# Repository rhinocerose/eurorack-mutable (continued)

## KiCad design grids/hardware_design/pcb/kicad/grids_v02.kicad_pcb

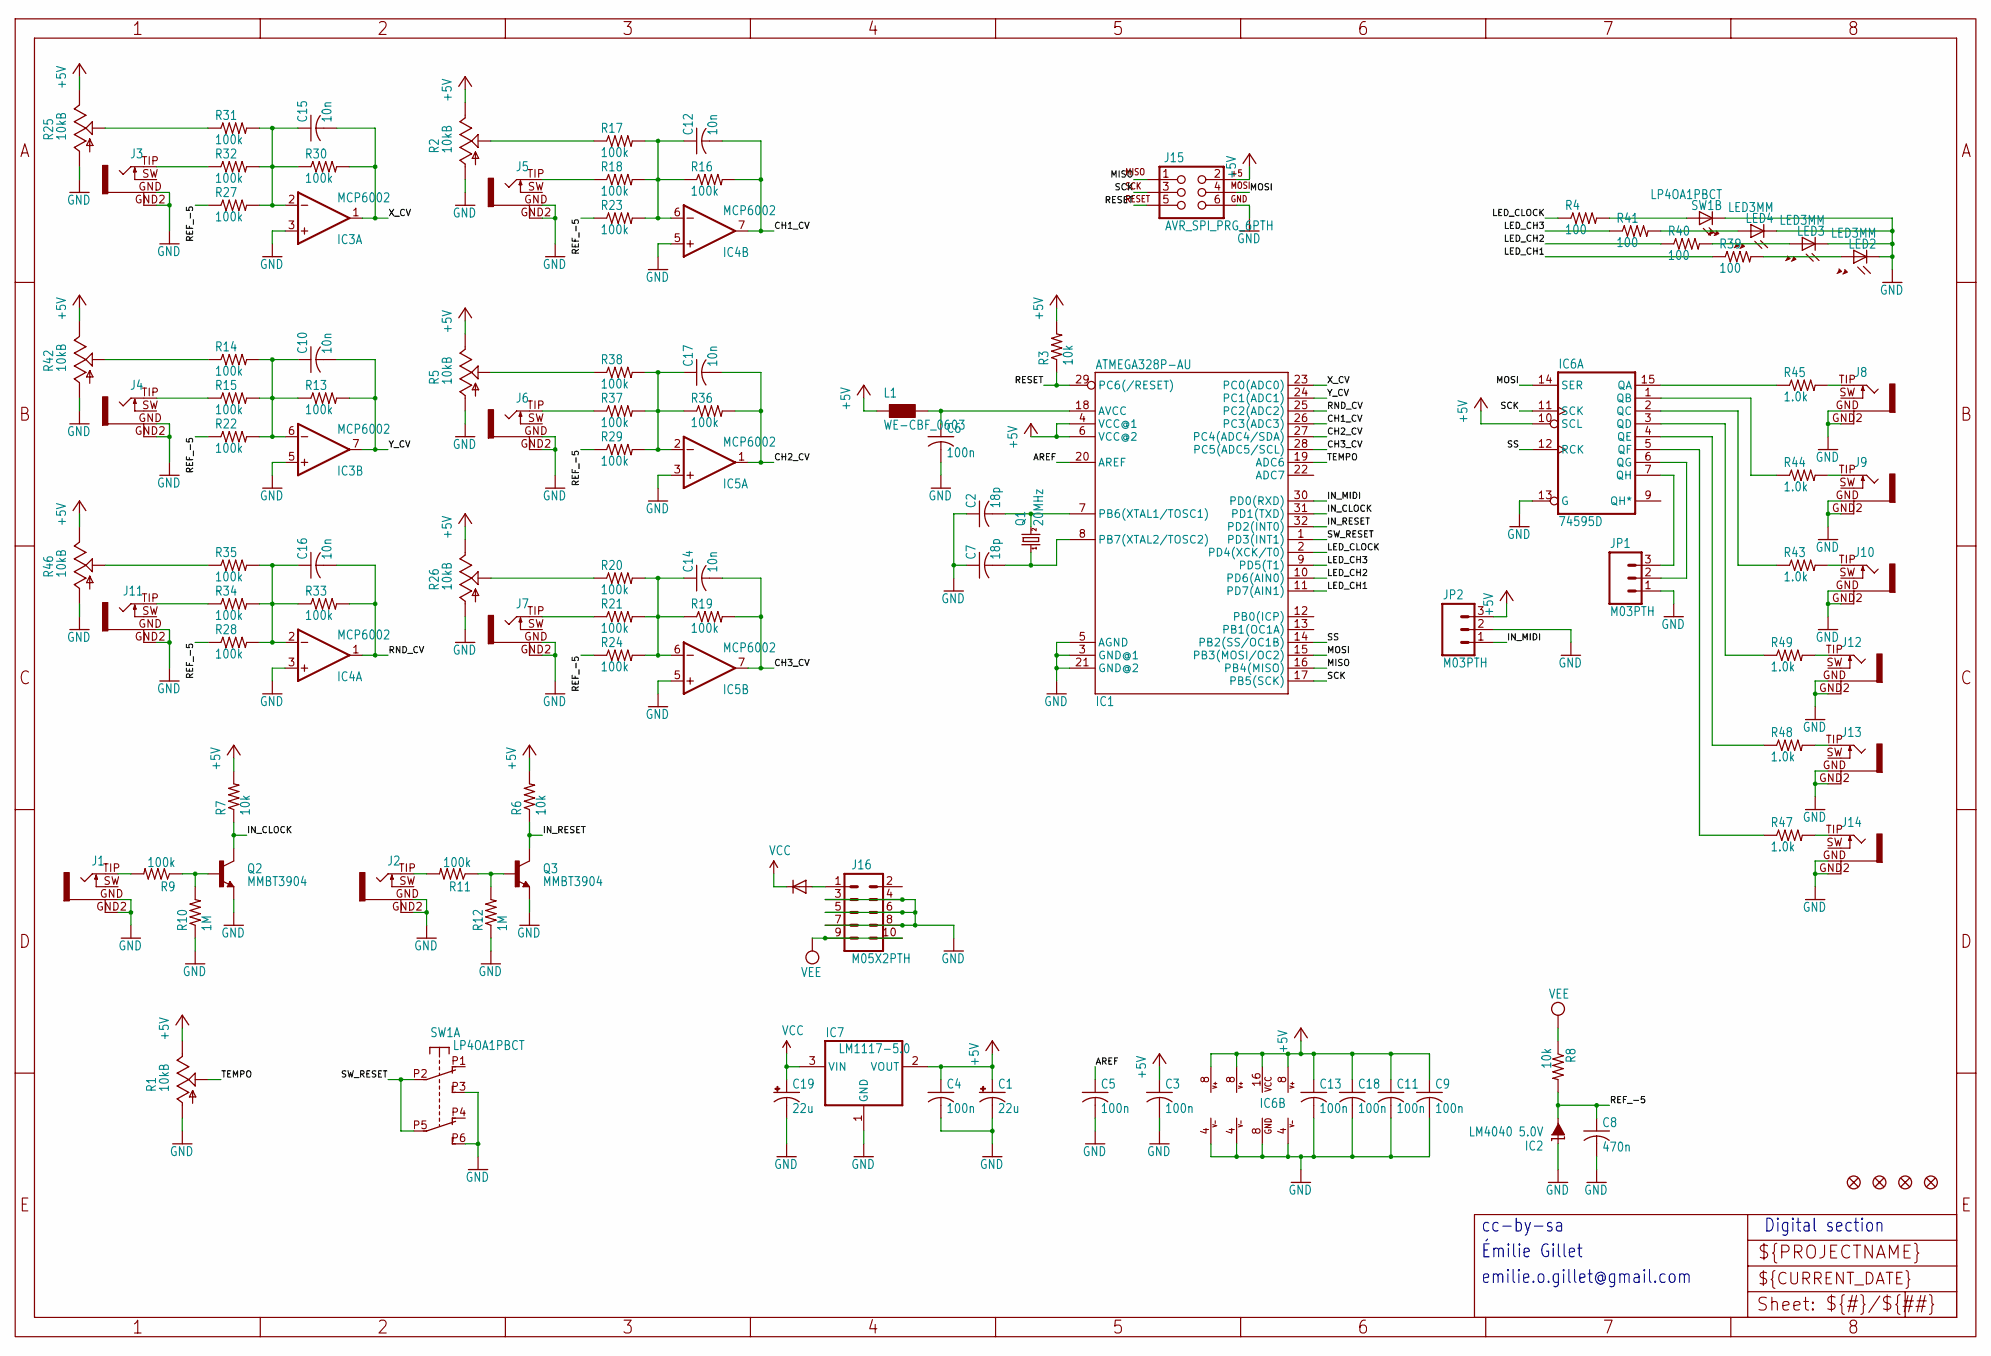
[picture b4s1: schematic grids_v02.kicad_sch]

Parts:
C1, C19: 22u; PANASONIC_C
C2, C7: 18p; C0603
C3, C4, C5, C6, C9, C11, C13, C18: 100n; C0603
C8: 470n; C0603
C10, C12, C14, C15, C16, C17: 10n; C0603
D1: 1N5819HW; SOD123
F1, F2, F3, F4: FIDUCIAL1X2; FIDUCIAL-1X2
IC1: ATMEGA328P-AU; TQFP32-08
IC2: LM4040 5.0V; DBZ_R-PDSO-G3
IC3, IC4, IC5: MCP6002; SO08
IC6: 74595D; SO16
IC7: LM1117-5.0; SOT223
J1, J2, J3, J4, J5, J6, J7, J8, J9, J10, J11, J12, J13, J14: PJ301WQP; WQP_PJ_301BM
J15: AVR_SPI_PRG_6PTH; 2X3
J16: M05X2PTH; AVR_ICSP
JP1, JP2: M03PTH; 1X03
L1: WE-CBF_0603; 0603
LED2, LED3, LED4: LED3MM
Q1: 20MHz; HC49UP
Q2, Q3: MMBT3904; SOT23-BEC
R1, R2, R5, R25, R26, R46: 10kB; ALPS_POT_VERTICAL_PS
R3, R6, R7, R8: 10k; R0603
R4, R39, R40, R41: 100; R0603
R9, R11, R13, R14, R15, R16, R17, R18, R19, R20, R21, R22, R23, R24, R27, R28, R29, R30, R31, R32, R33, R34, R35, R36, R37, R38: 100k; R0603
R10, R12: 1M; R0603
R42: 10kB; ALPS_POT_VERTICAL_PS4
R43, R44, R45, R47, R48, R49: 1.0k; R0603
SW1: LP4OA1PBCT

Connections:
+5V: C1.+, C3.1, C4.1, C9.1, C11.1, C13.1, C18.1, IC1.4 (VCC@1), IC1.6 (VCC@2), IC3.8 (V+), IC4.8 (V+), IC5.8 (V+), IC6.10 (SCL), IC6.16 (VCC), IC7.2 (VOUT), J15.2, JP2.3, L1.1, R1.P$1 (E), R2.P$1 (E), R3.2, R5.P$1 (E), R6.2, R7.2, R25.P$1 (E), R26.P$1 (E), R42.P$1 (E), R46.P$1 (E)
AREF: C5.1, IC1.20 (AREF)
CH1_CV: C12.2, IC1.26 (PC3(ADC3)), IC4.7 (OUT), R16.2
CH2_CV: C17.2, IC1.27 (PC4(ADC4/SDA)), IC5.1 (OUT), R36.2
CH3_CV: C14.2, IC1.28 (PC5(ADC5/SCL)), IC5.7 (OUT), R19.2
CLOCK_OUT: IC6.6 (QG), JP1.2
GATE1_IN: J1.TIP (2), R9.2
GATE1_LED: R4.2, SW1.L1
GATE2_IN: J2.TIP (2), R11.2
GATE2_LED: LED4.A, R41.2
GATE3_LED: LED3.A, R40.2
GATE4_LED: LED2.A, R39.2
GND: C1.-, C2.1, C3.2, C4.2, C5.2, C6.2, C7.1, C8.2, C9.2, C11.2, C13.2, C18.2, C19.-, IC1.3 (GND@1), IC1.5 (AGND), IC1.21 (GND@2), IC2.1 (C), IC3.3 (+IN), IC3.4 (V-), IC3.5 (+IN), IC4.3 (+IN), IC4.4 (V-), IC4.5 (+IN), IC5.3 (+IN), IC5.4 (V-), IC5.5 (+IN), IC6.8 (GND), IC6.13 (G), IC7.1 (GND), J1.GND (1), J1.GND2 (4), J2.GND (1), J2.GND2 (4), J3.GND (1), J3.GND2 (4), J4.GND (1), J4.GND2 (4), J5.GND (1), J5.GND2 (4), J6.GND (1), J6.GND2 (4), J7.GND (1), J7.GND2 (4), J8.GND (1), J8.GND2 (4), J9.GND (1), J9.GND2 (4), J10.GND (1), J10.GND2 (4), J11.GND (1), J11.GND2 (4), J12.GND (1), J12.GND2 (4), J13.GND (1), J13.GND2 (4), J14.GND (1), J14.GND2 (4), J15.6, J16.3, J16.4, J16.5, J16.6, J16.7, J16.8, JP1.1, JP2.2, LED2.K (C), LED3.K (C), LED4.K (C), Q2.E, Q3.E, R1.P$3 (A), R2.P$3 (A), R5.P$3 (A), R10.1, R12.1, R25.P$3 (A), R26.P$3 (A), R42.P$3 (A), R46.P$3 (A), SW1.L2, SW1.P3 (A3), SW1.P6 (B3)
IN_CLOCK: IC1.31 (PD1(TXD)), Q2.C, R7.1
IN_MIDI: IC1.30 (PD0(RXD)), JP2.1
IN_RESET: IC1.32 (PD2(INT0)), Q3.C, R6.1
LED_CH1: IC1.11 (PD7(AIN1)), R39.1
LED_CH2: IC1.10 (PD6(AIN0)), R40.1
LED_CH3: IC1.9 (PD5(T1)), R41.1
LED_CLOCK: IC1.2 (PD4(XCK/T0)), R4.1
MISO: IC1.16 (PB4(MISO)), J15.1
MOSI: IC1.15 (PB3(MOSI/OC2)), IC6.14 (SER), J15.4
unnamed: Q2.B, R9.1, R10.2
unnamed: Q3.B, R11.1, R12.2
unnamed: D1.A, J16.1
unnamed: J14.TIP (2), R47.2
unnamed: J13.TIP (2), R48.2
unnamed: J12.TIP (2), R49.2
unnamed: R25.P$2 (S), R31.1
unnamed: J3.TIP (2), R32.1
unnamed: C10.1, IC3.6 (-IN), R13.1, R14.2, R15.2, R22.2
unnamed: R14.1, R42.P$2 (S)
unnamed: J4.TIP (2), R15.1
unnamed: C16.1, IC4.2 (-IN), R28.2, R33.1, R34.2, R35.2
unnamed: R35.1, R46.P$2 (S)
unnamed: J11.TIP (2), R34.1
unnamed: C12.1, IC4.6 (-IN), R16.1, R17.2, R18.2, R23.2
unnamed: R2.P$2 (S), R17.1
unnamed: J5.TIP (2), R18.1
unnamed: C17.1, IC5.2 (-IN), R29.2, R36.1, R37.2, R38.2
unnamed: R5.P$2 (S), R38.1
unnamed: J6.TIP (2), R37.1
unnamed: C14.1, IC5.6 (-IN), R19.1, R20.2, R21.2, R24.2
unnamed: R20.1, R26.P$2 (S)
unnamed: J7.TIP (2), R21.1
unnamed: IC6.15 (QA), R45.1
unnamed: IC6.1 (QB), R44.1
unnamed: C15.1, IC3.2 (-IN), R27.2, R30.1, R31.2, R32.2
unnamed: IC6.2 (QC), R43.1
unnamed: IC6.3 (QD), R49.1
unnamed: IC6.4 (QE), R48.1
unnamed: IC6.5 (QF), R47.1
unnamed: J8.TIP (2), R45.2
unnamed: J9.TIP (2), R44.2
unnamed: J10.TIP (2), R43.2
unnamed: C6.1, IC1.18 (AVCC), L1.2
unnamed: C7.2, IC1.8 (PB7(XTAL2/TOSC2)), Q1.1
unnamed: C2.2, IC1.7 (PB6(XTAL1/TOSC1)), Q1.2
RANDOM_GATE: IC6.7 (QH), JP1.3
REF_-5: C8.1, IC2.2 (A), R8.2, R22.1, R23.1, R24.1, R27.1, R28.1, R29.1
RESET: IC1.29 (PC6(/RESET)), J15.5, R3.1
RND_CV: C16.2, IC1.25 (PC2(ADC2)), IC4.1 (OUT), R33.2
SCK: IC1.17 (PB5(SCK)), IC6.11 (SCK), J15.3
SS: IC1.14 (PB2(SS/OC1B)), IC6.12 (RCK)
SW_RESET: IC1.1 (PD3(INT1)), SW1.P2 (A2), SW1.P5 (B2)
TEMPO: IC1.19 (ADC6), R1.P$2 (S)
VCC: C19.+, D1.C, IC7.3 (VIN)
VEE: J16.9, J16.10, R8.1
X_CV: C15.2, IC1.23 (PC0(ADC0)), IC3.1 (OUT), R30.2
Y_CV: C10.2, IC1.24 (PC1(ADC1)), IC3.7 (OUT), R13.2

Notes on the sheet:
Digital section
Émilie Gillet
emilie.o.gillet@gmail.com
cc-by-sa

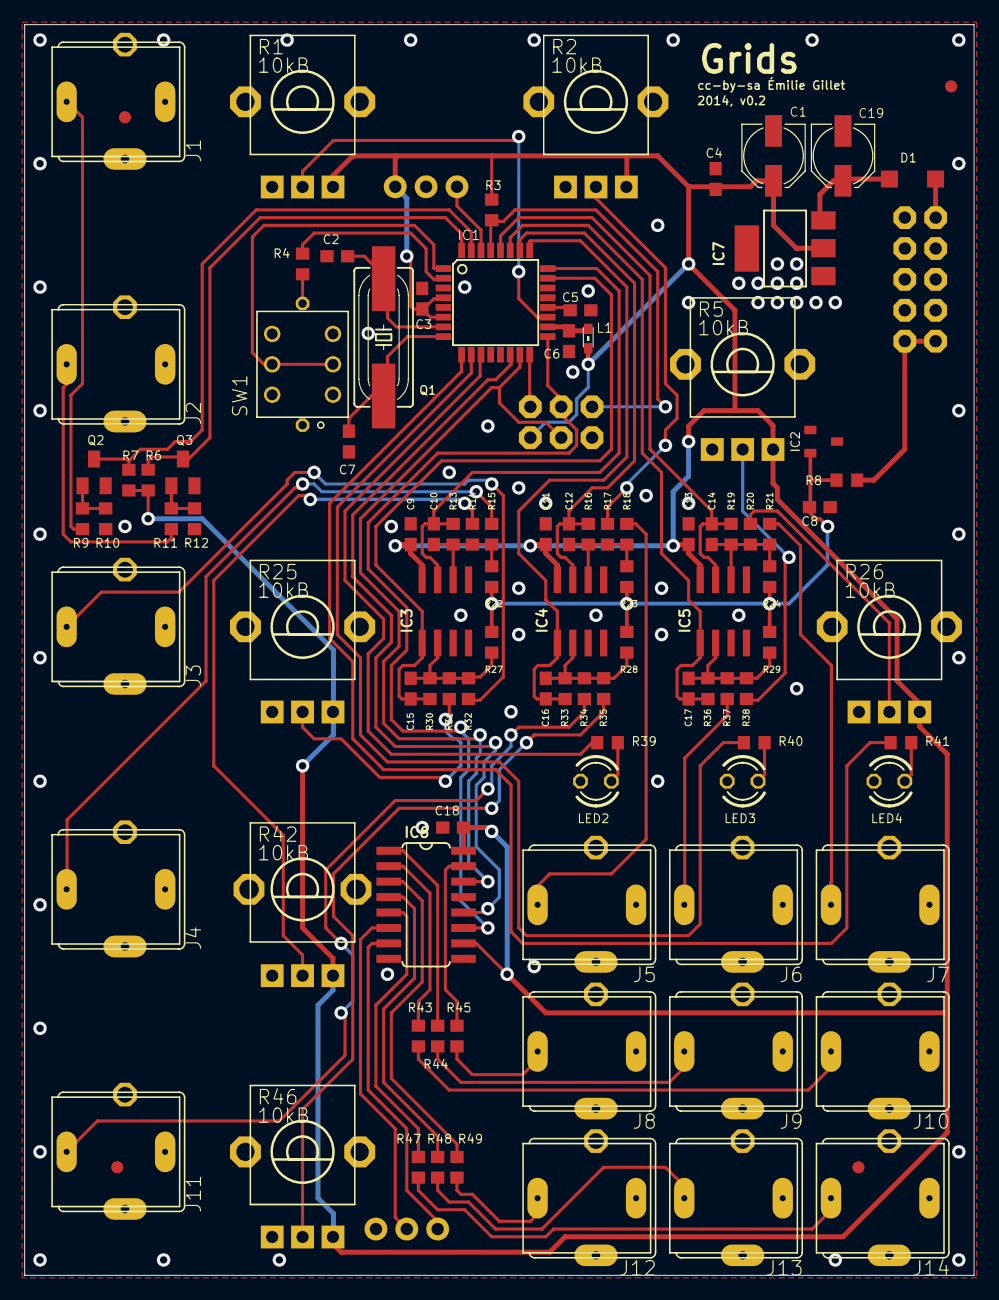
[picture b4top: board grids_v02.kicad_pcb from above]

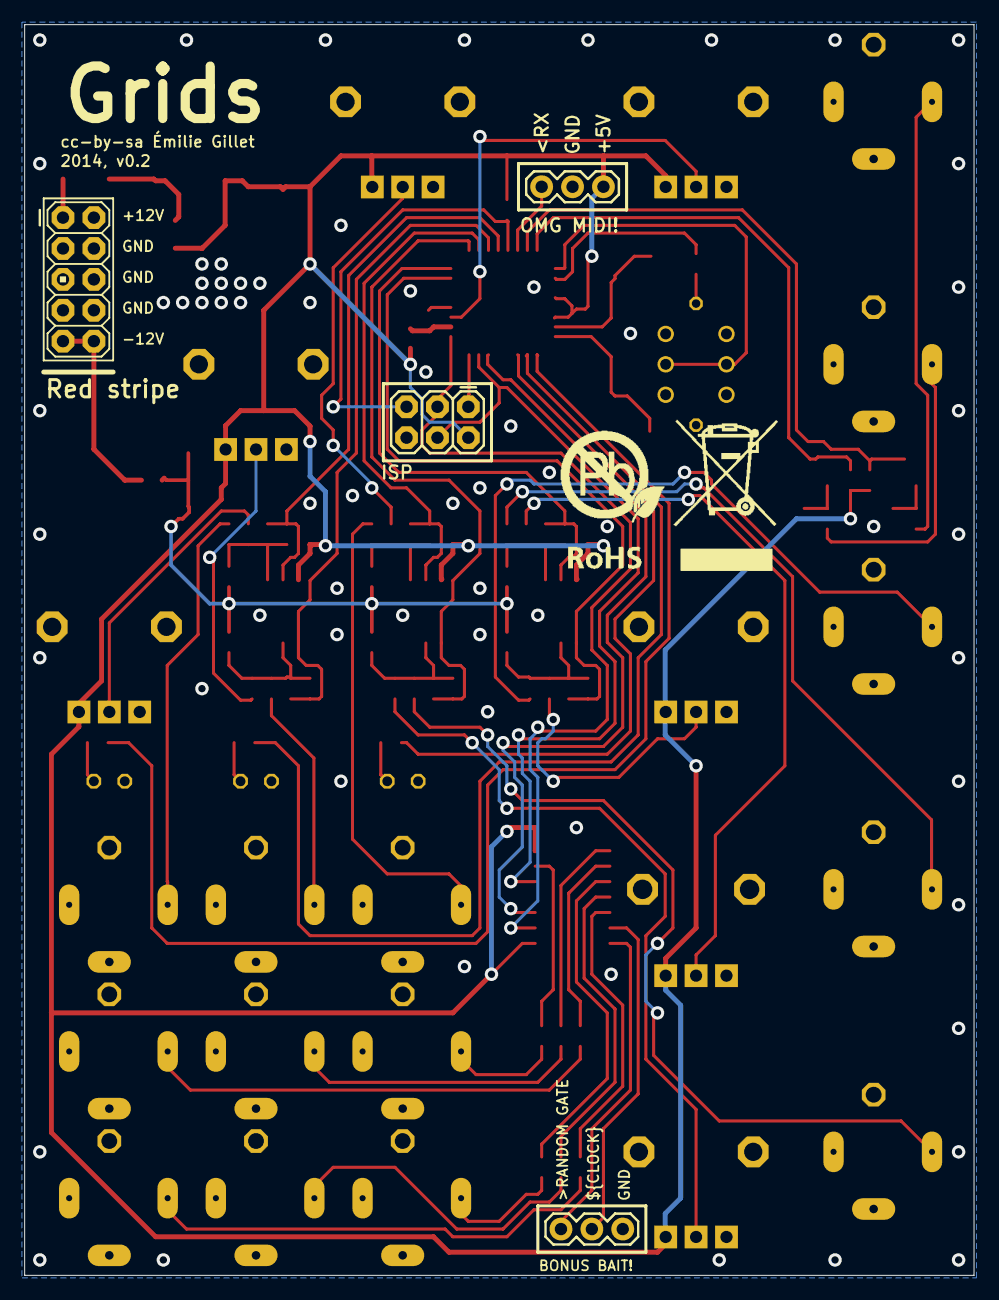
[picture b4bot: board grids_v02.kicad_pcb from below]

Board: 2 copper layers, 78.1 x 102.9 mm, 108 parts (5 on the bottom side), 70 nets.

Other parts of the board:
U$1: EURORACK_TEMPLATE
U$2: ROHS_BIG

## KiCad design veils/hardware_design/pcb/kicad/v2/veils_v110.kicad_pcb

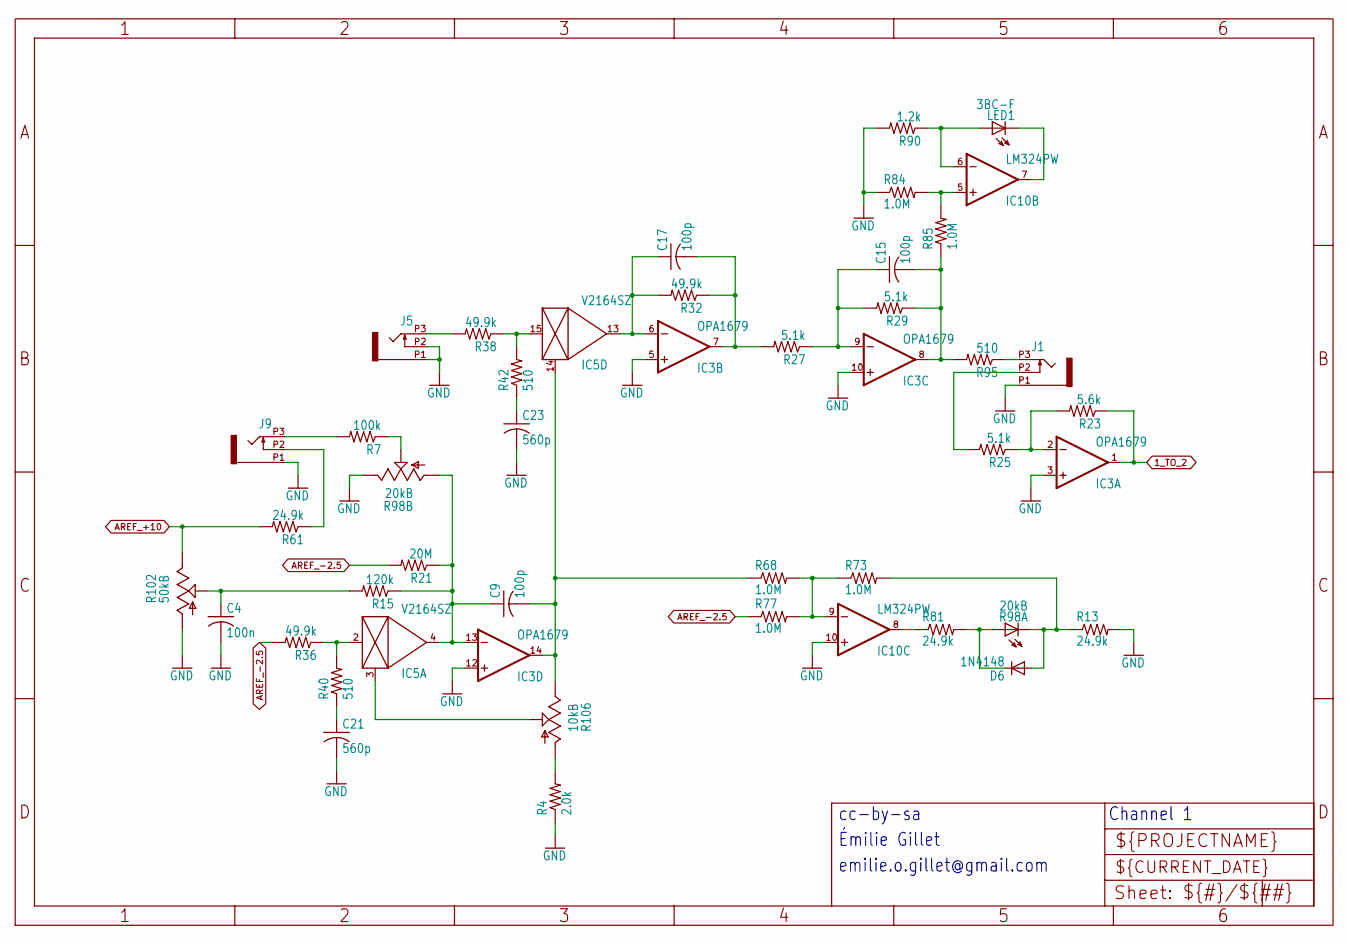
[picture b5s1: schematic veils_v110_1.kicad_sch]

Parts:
C4: 100n; C0402
C9, C15, C17: 100p; C0402
C21, C23: 560p; C0402
D6: 1N4148; SOD523
IC3: OPA1679; TSSOP14_065
IC5: V2164SZ; SOIC16N
IC10: LM324PW; TSSOP14_065
J1, J5, J9: PJ301_THONKICONNTME; WQP_PJ_301M_TME
LED1: 3BC-F; LED3MM
R4: 2.0k; R0402
R7: 100k; R0402
R13, R61, R81: 24.9k; R0402
R15: 120k; R0402
R21: 20M; R0402
R23: 5.6k; R0402
R25, R27, R29: 5.1k; R0402
R32, R36, R38: 49.9k; R0402
R40, R42: 510; R0402
R68, R73, R77, R84, R85: 1.0M; R0402
R90: 1.2k; R0402
R95: 510; R0603
R98: 20kB; BOURNS_SLIDER
R102: 50kB; ALPS_POT_NARROW
R106: 10kB; ALPS_POT_NARROW

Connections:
1_TO_2: IC3.1 (OUT), R23.1; also elsewhere on the board
AREF_+10: R61.2, R102.P$1 (E); also elsewhere on the board
AREF_-2.5: R21.2, R36.2, R77.1; also elsewhere on the board
CV_IN_1: J9.P3 (3), R7.2
FOO: IC5.2 (IN), R36.1, R40.2
GND: C4.2, C21.2, C23.2, IC3.3 (+IN), IC3.5 (+IN), IC3.10 (+IN), IC3.12 (+IN), IC10.10 (+IN), J1.P1 (1), J5.P1 (1), J5.P2 (2), J9.P1 (1), R4.1, R13.2, R84.1, R90.2, R98.3 (E), R102.P$3 (A); also elsewhere on the board
unnamed: IC10.5 (+IN), R84.2, R85.2
unnamed: J1.P3 (3), R95.1
unnamed: IC5.3 (CTRL), R106.P$2 (S)
unnamed: C15.1, IC3.9 (-IN), R27.1, R29.2
unnamed: C4.1, R15.2, R102.P$2 (S)
unnamed: R4.2, R106.P$3 (A)
unnamed: IC10.7 (OUT), LED1.K (C)
unnamed: IC10.6 (-IN), LED1.A, R90.1
unnamed: C21.1, R40.1
unnamed: IC3.2 (-IN), R23.2, R25.1
unnamed: J1.P2 (2), R25.2
unnamed: J9.P2 (2), R61.1
unnamed: R7.1, R98.2 (S)
unnamed: C23.1, R42.1
unnamed: IC10.8 (OUT), R81.1
unnamed: D6.A, R13.1, R73.2, R98.E (C)
unnamed: IC10.9 (-IN), R68.2, R73.1, R77.2
unnamed: C9.1, IC3.13 (-IN), IC5.4 (OUT), R15.1, R21.1, R98.1 (A)
unnamed: J5.P3 (3), R38.2
unnamed: IC5.15 (IN), R38.1, R42.2
unnamed: C9.2, IC3.14 (OUT), IC5.14 (CTRL), R68.1, R106.P$1 (E)
unnamed: C17.1, IC3.6 (-IN), IC5.13 (OUT), R32.2
unnamed: C17.2, IC3.7 (OUT), R27.2, R32.1
OUT1: C15.2, IC3.8 (OUT), R29.1, R85.1, R95.2
PROT1: D6.C, R81.2, R98.B (A)

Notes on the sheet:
cc-by-sa
emilie.o.gillet@gmail.com
Channel 1
Émilie Gillet

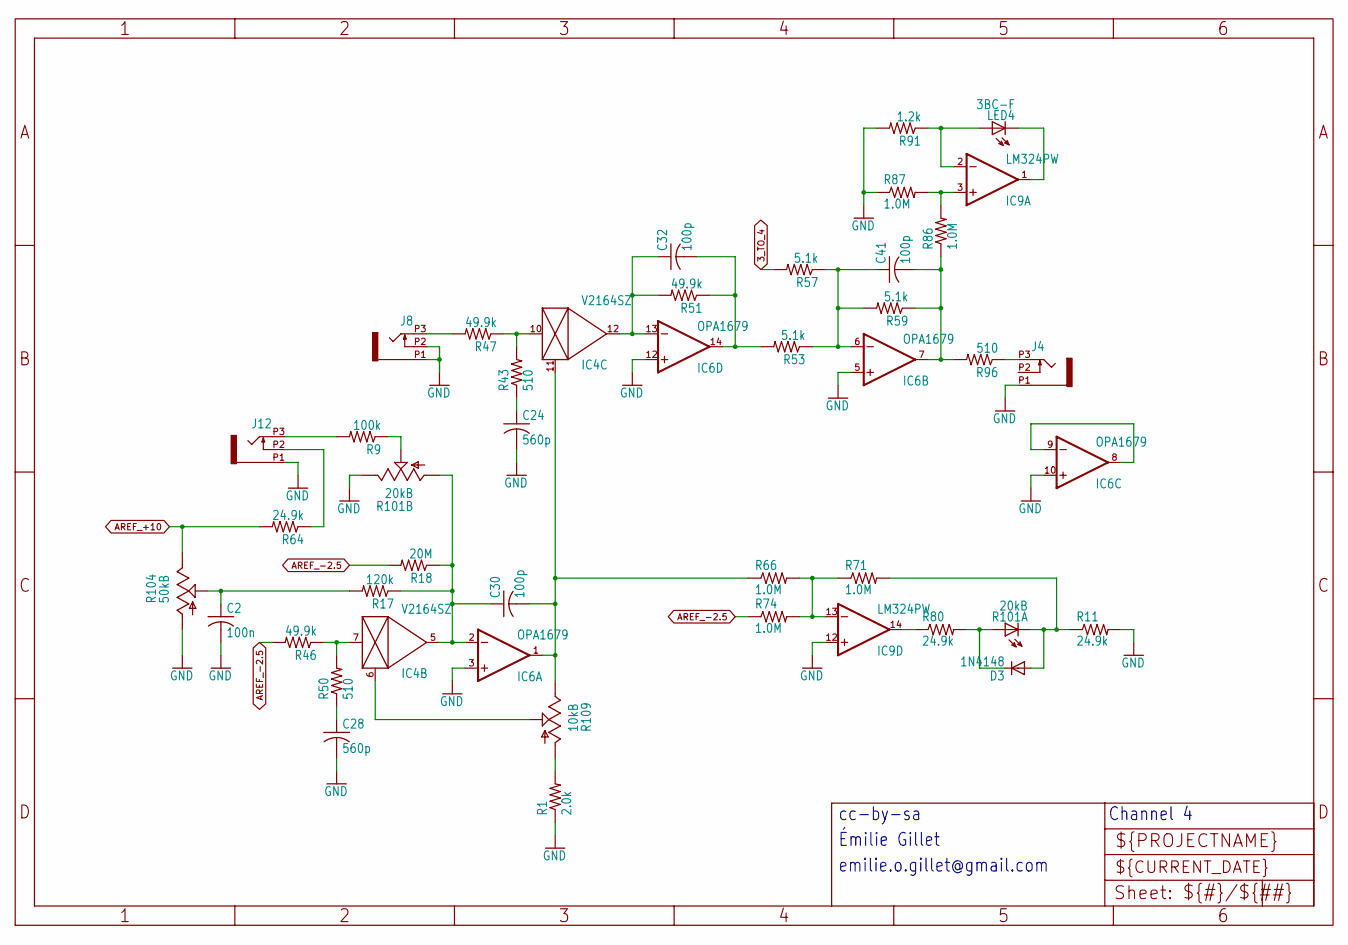
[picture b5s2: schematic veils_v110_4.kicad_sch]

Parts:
C2: 100n; C0402
C24, C28: 560p; C0402
C30, C32, C41: 100p; C0402
D3: 1N4148; SOD523
IC4: V2164SZ; SOIC16N
IC6: OPA1679; TSSOP14_065
IC9: LM324PW; TSSOP14_065
J4, J8, J12: PJ301_THONKICONNTME; WQP_PJ_301M_TME
LED4: 3BC-F; LED3MM
R1: 2.0k; R0402
R9: 100k; R0402
R11, R64, R80: 24.9k; R0402
R17: 120k; R0402
R18: 20M; R0402
R43, R50: 510; R0402
R46, R47, R51: 49.9k; R0402
R53, R57, R59: 5.1k; R0402
R66, R71, R74, R86, R87: 1.0M; R0402
R91: 1.2k; R0402
R96: 510; R0603
R101: 20kB; BOURNS_SLIDER
R104: 50kB; ALPS_POT_NARROW
R109: 10kB; ALPS_POT_NARROW

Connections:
3_TO_4: R57.2; also elsewhere on the board
AREF_+10: R64.2, R104.P$1 (E); also elsewhere on the board
AREF_-2.5: R18.2, R46.2, R74.1; also elsewhere on the board
FOO3: IC4.7 (IN), R46.1, R50.2
GND: C2.2, C24.2, C28.2, IC6.3 (+IN), IC6.5 (+IN), IC6.10 (+IN), IC6.12 (+IN), IC9.12 (+IN), J4.P1 (1), J8.P1 (1), J8.P2 (2), J12.P1 (1), R1.1, R11.2, R87.1, R91.2, R101.3 (E), R104.P$3 (A); also elsewhere on the board
unnamed: IC6.8 (OUT), IC6.9 (-IN)
unnamed: IC9.3 (+IN), R86.2, R87.2
unnamed: IC4.6 (CTRL), R109.P$2 (S)
unnamed: J12.P2 (2), R64.1
unnamed: R1.2, R109.P$3 (A)
unnamed: J12.P3 (3), R9.2
unnamed: C32.1, IC4.12 (OUT), IC6.13 (-IN), R51.2
unnamed: J8.P3 (3), R47.2
unnamed: R9.1, R101.2 (S)
unnamed: J4.P3 (3), R96.1
unnamed: C24.1, R43.1
unnamed: IC4.10 (IN), R43.2, R47.1
unnamed: C41.1, IC6.6 (-IN), R53.1, R57.1, R59.2
unnamed: IC9.1 (OUT), LED4.K (C)
unnamed: IC9.2 (-IN), LED4.A, R91.1
unnamed: IC9.14 (OUT), R80.1
unnamed: C32.2, IC6.14 (OUT), R51.1, R53.2
unnamed: C28.1, R50.1
unnamed: C30.1, IC4.5 (OUT), IC6.2 (-IN), R17.1, R18.1, R101.1 (A)
unnamed: D3.A, R11.1, R71.2, R101.E (C)
unnamed: IC9.13 (-IN), R66.2, R71.1, R74.2
unnamed: C30.2, IC4.11 (CTRL), IC6.1 (OUT), R66.1, R109.P$1 (E)
unnamed: C2.1, R17.2, R104.P$2 (S)
OUT4: C41.2, IC6.7 (OUT), R59.1, R86.1, R96.2
PROT4: D3.C, R80.2, R101.B (A)

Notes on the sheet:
cc-by-sa
emilie.o.gillet@gmail.com
Channel 4
Émilie Gillet

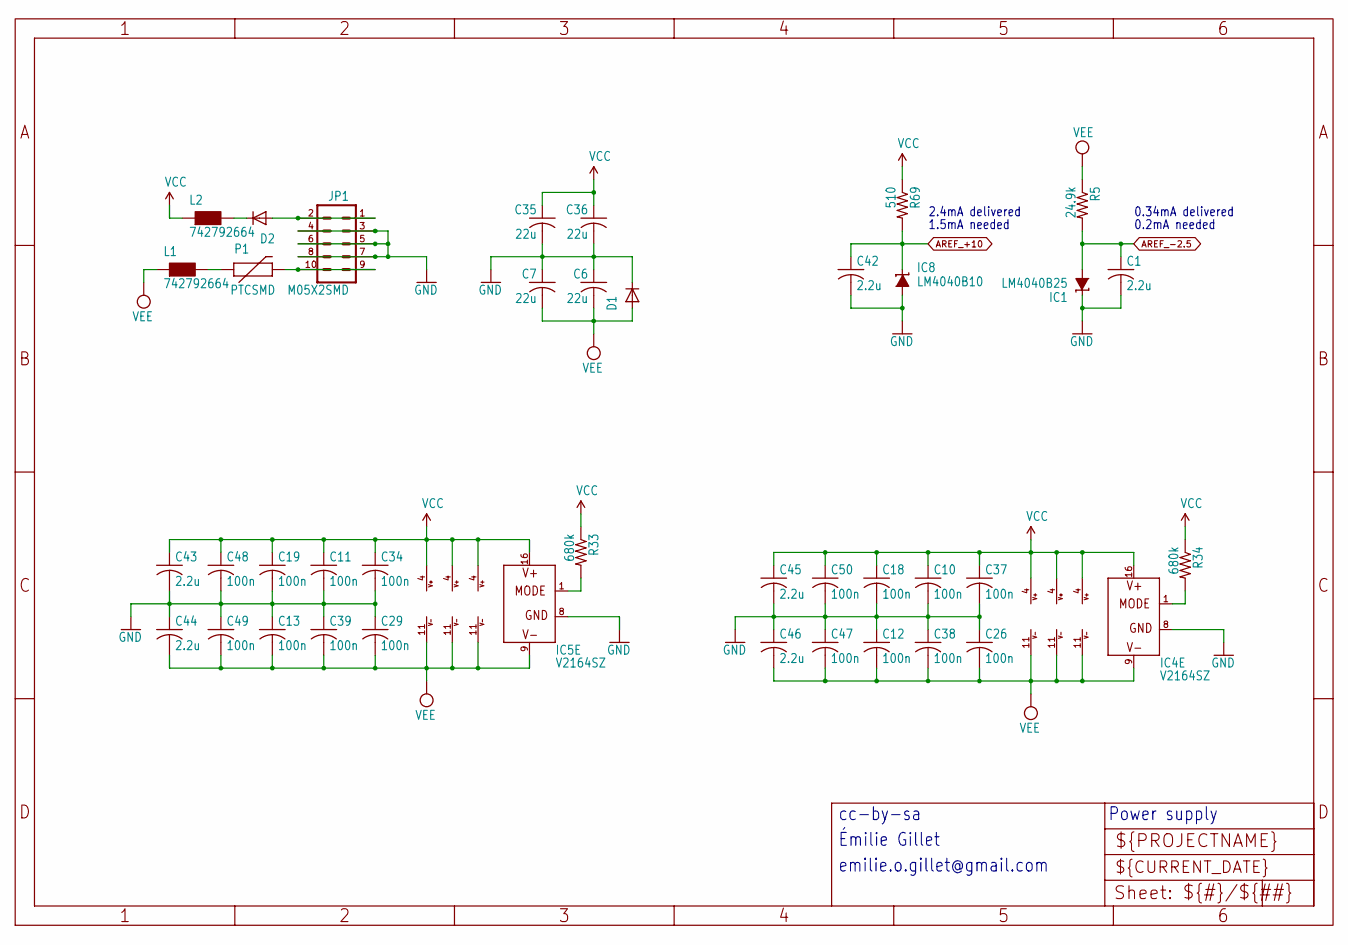
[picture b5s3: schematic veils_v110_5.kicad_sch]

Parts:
C1, C42, C43, C44, C45, C46: 2.2u; C0603
C6, C7, C35, C36: 22u; C1206
C10, C11, C12, C13, C18, C19, C26, C29, C34, C37, C38, C39, C47, C48, C49, C50: 100n; C0402
D1, D2: 1N5819HW; SOD123
IC1: LM4040B25; DBZ_R-PDSO-G3
IC2, IC3, IC6, IC7: OPA1679; TSSOP14_065
IC4, IC5: V2164SZ; SOIC16N
IC8: LM4040B10; DBZ_R-PDSO-G3
IC9, IC10: LM324PW; TSSOP14_065
JP1: M05X2SMD; 2X5-SMD
L1, L2: 742792664; 0603
P1: PTCSMD; PTC-1206
R5: 24.9k; R0402
R33, R34: 680k; R0402
R69: 510; R0402

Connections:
AREF_+10: C42.1, IC8.1 (C), R69.2; also elsewhere on the board
AREF_-2.5: C1.1, IC1.2 (A), R5.2; also elsewhere on the board
GND: C1.2, C6.1, C7.1, C10.2, C11.2, C12.1, C13.1, C18.2, C19.2, C26.1, C29.1, C34.2, C35.2, C36.2, C37.2, C38.1, C39.1, C42.2, C43.2, C44.1, C45.2, C46.1, C47.1, C48.2, C49.1, C50.2, D1.C, IC1.1 (C), IC4.8 (GND), IC5.8 (GND), IC8.2 (A), JP1.3, JP1.4, JP1.5, JP1.6, JP1.7, JP1.8; also elsewhere on the board
unnamed: D2.A, JP1.1, JP1.2
unnamed: JP1.9, JP1.10, P1.2
unnamed: L1.2, P1.1
unnamed: D2.C, L2.2
unnamed: IC5.1 (MODE), R33.2
unnamed: IC4.1 (MODE), R34.2
VCC: C10.1, C11.1, C18.1, C19.1, C34.1, C35.1, C36.1, C37.1, C43.1, C45.1, C48.1, C50.1, IC2.4 (V+), IC3.4 (V+), IC4.16 (V+), IC5.16 (V+), IC6.4 (V+), IC7.4 (V+), IC9.4 (V+), IC10.4 (V+), L2.1, R33.1, R34.1, R69.1
VEE: C6.2, C7.2, C12.2, C13.2, C26.2, C29.2, C38.2, C39.2, C44.2, C46.2, C47.2, C49.2, D1.A, IC2.11 (V-), IC3.11 (V-), IC4.9 (V-), IC5.9 (V-), IC6.11 (V-), IC7.11 (V-), IC9.11 (V-), IC10.11 (V-), L1.1, R5.1

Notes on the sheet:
0.34mA delivered
1.5mA needed
Power supply
0.2mA needed
Émilie Gillet
2.4mA delivered
emilie.o.gillet@gmail.com
cc-by-sa

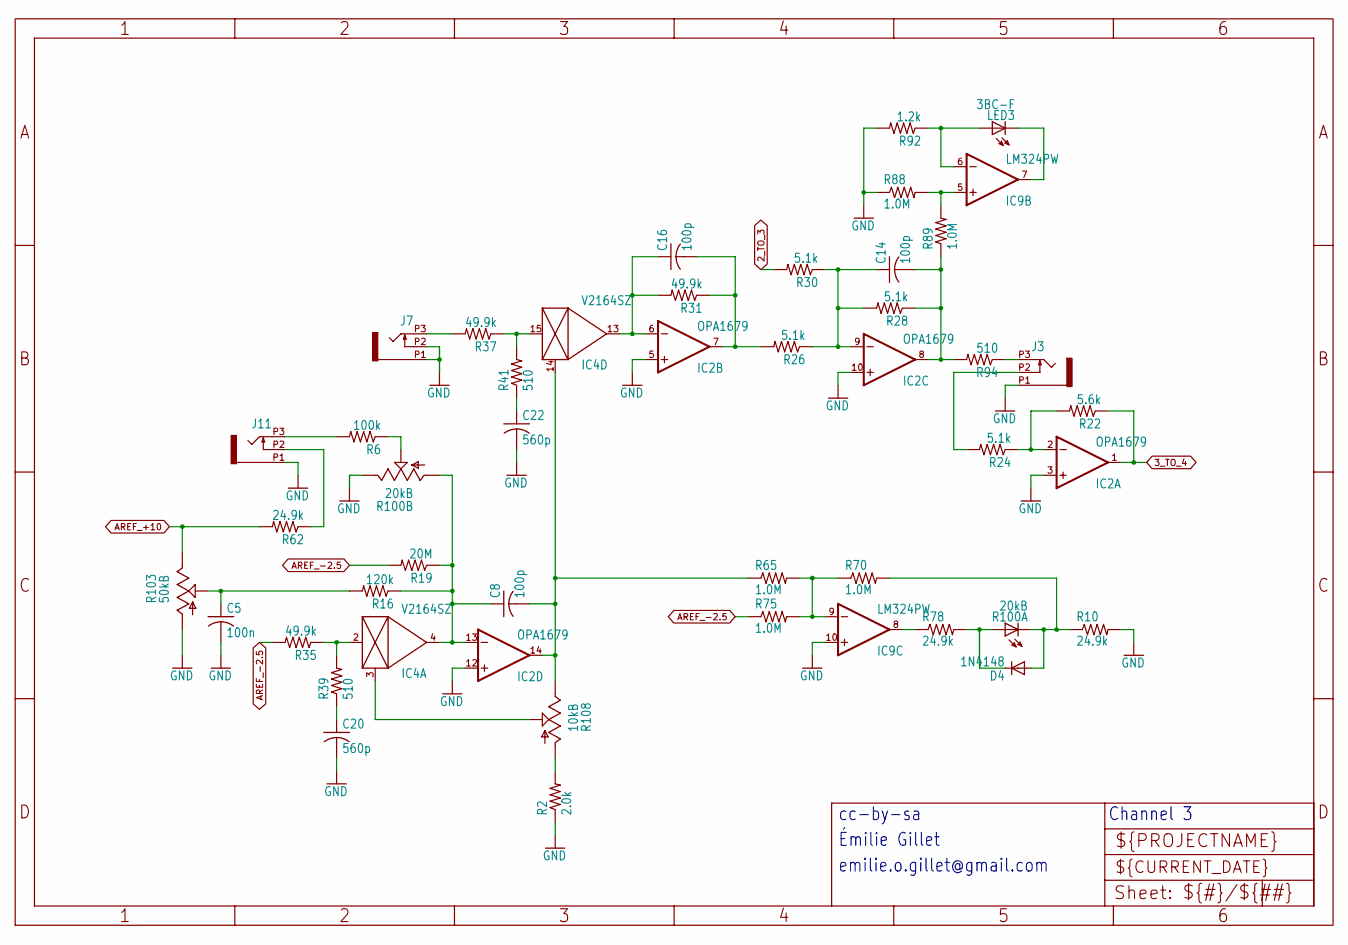
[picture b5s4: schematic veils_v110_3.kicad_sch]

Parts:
C5: 100n; C0402
C8, C14, C16: 100p; C0402
C20, C22: 560p; C0402
D4: 1N4148; SOD523
IC2: OPA1679; TSSOP14_065
IC4: V2164SZ; SOIC16N
IC9: LM324PW; TSSOP14_065
J3, J7, J11: PJ301_THONKICONNTME; WQP_PJ_301M_TME
LED3: 3BC-F; LED3MM
R2: 2.0k; R0402
R6: 100k; R0402
R10, R62, R78: 24.9k; R0402
R16: 120k; R0402
R19: 20M; R0402
R22: 5.6k; R0402
R24, R26, R28, R30: 5.1k; R0402
R31, R35, R37: 49.9k; R0402
R39, R41: 510; R0402
R65, R70, R75, R88, R89: 1.0M; R0402
R92: 1.2k; R0402
R94: 510; R0603
R100: 20kB; BOURNS_SLIDER
R103: 50kB; ALPS_POT_NARROW
R108: 10kB; ALPS_POT_NARROW

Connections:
2_TO_3: R30.2; also elsewhere on the board
3_TO_4: IC2.1 (OUT), R22.1; also elsewhere on the board
AREF_+10: R62.2, R103.P$1 (E); also elsewhere on the board
AREF_-2.5: R19.2, R35.2, R75.1; also elsewhere on the board
FOO2: IC4.2 (IN), R35.1, R39.2
GND: C5.2, C20.2, C22.2, IC2.3 (+IN), IC2.5 (+IN), IC2.10 (+IN), IC2.12 (+IN), IC9.10 (+IN), J3.P1 (1), J7.P1 (1), J7.P2 (2), J11.P1 (1), R2.1, R10.2, R88.1, R92.2, R100.3 (E), R103.P$3 (A); also elsewhere on the board
unnamed: IC9.5 (+IN), R88.2, R89.2
unnamed: J3.P3 (3), R94.1
unnamed: IC4.3 (CTRL), R108.P$2 (S)
unnamed: R2.2, R108.P$3 (A)
unnamed: J11.P3 (3), R6.2
unnamed: C22.1, R41.1
unnamed: IC4.15 (IN), R37.1, R41.2
unnamed: C14.1, IC2.9 (-IN), R26.1, R28.2, R30.1
unnamed: J7.P3 (3), R37.2
unnamed: C16.1, IC2.6 (-IN), IC4.13 (OUT), R31.2
unnamed: IC9.7 (OUT), LED3.K (C)
unnamed: IC9.6 (-IN), LED3.A, R92.1
unnamed: IC2.2 (-IN), R22.2, R24.1
unnamed: J3.P2 (2), R24.2
unnamed: C20.1, R39.1
unnamed: R6.1, R100.2 (S)
unnamed: C8.1, IC2.13 (-IN), IC4.4 (OUT), R16.1, R19.1, R100.1 (A)
unnamed: IC9.8 (OUT), R78.1
unnamed: D4.A, R10.1, R70.2, R100.E (C)
unnamed: IC9.9 (-IN), R65.2, R70.1, R75.2
unnamed: C8.2, IC2.14 (OUT), IC4.14 (CTRL), R65.1, R108.P$1 (E)
unnamed: J11.P2 (2), R62.1
unnamed: C5.1, R16.2, R103.P$2 (S)
unnamed: C16.2, IC2.7 (OUT), R26.2, R31.1
OUT3: C14.2, IC2.8 (OUT), R28.1, R89.1, R94.2
PROT3: D4.C, R78.2, R100.B (A)

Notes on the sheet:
emilie.o.gillet@gmail.com
cc-by-sa
Émilie Gillet
Channel 3

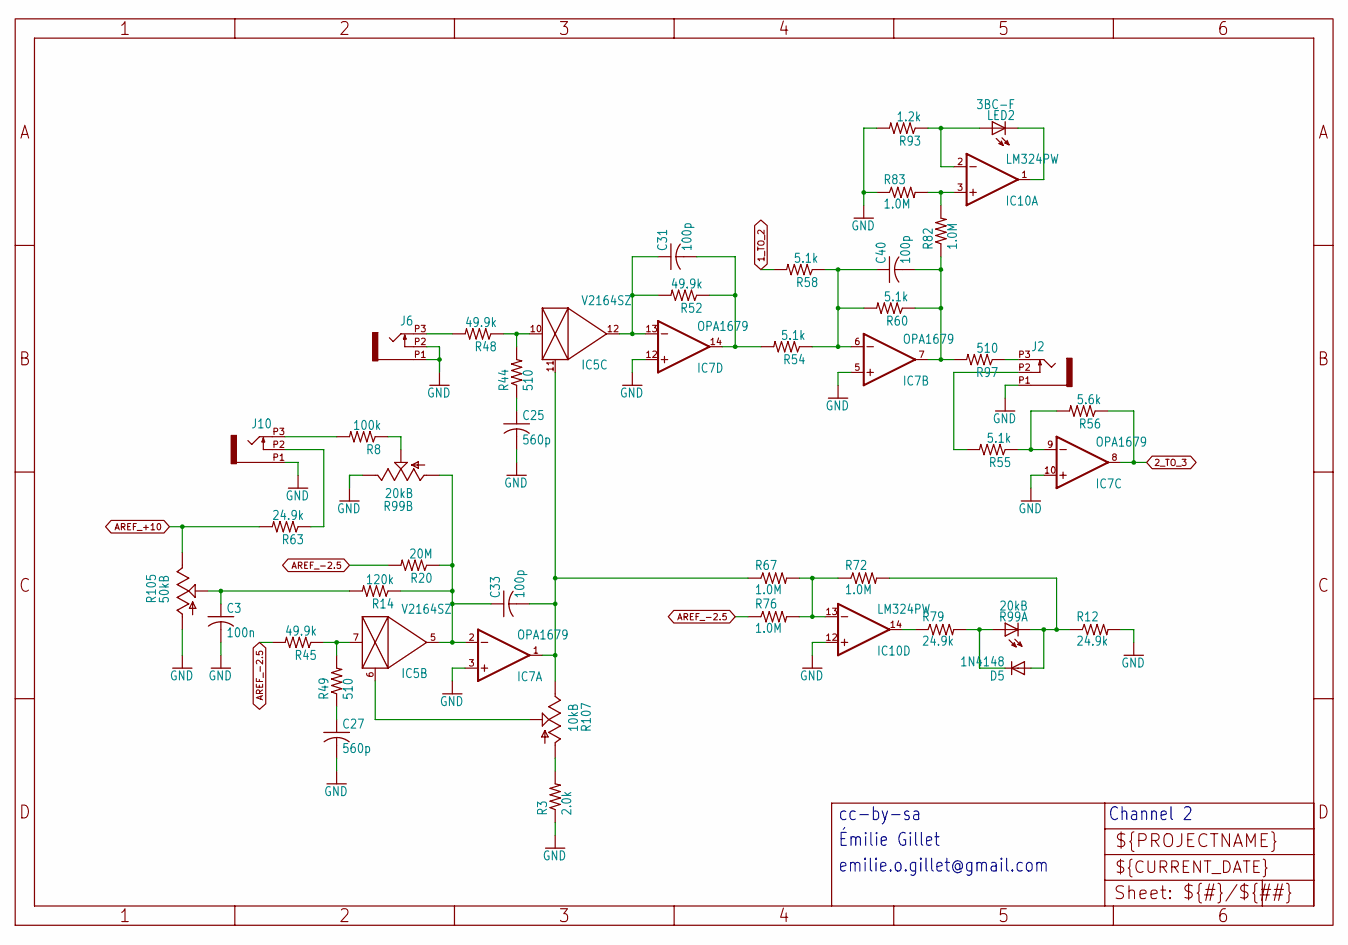
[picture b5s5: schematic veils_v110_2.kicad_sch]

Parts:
C3: 100n; C0402
C25, C27: 560p; C0402
C31, C33, C40: 100p; C0402
D5: 1N4148; SOD523
IC5: V2164SZ; SOIC16N
IC7: OPA1679; TSSOP14_065
IC10: LM324PW; TSSOP14_065
J2, J6, J10: PJ301_THONKICONNTME; WQP_PJ_301M_TME
LED2: 3BC-F; LED3MM
R3: 2.0k; R0402
R8: 100k; R0402
R12, R63, R79: 24.9k; R0402
R14: 120k; R0402
R20: 20M; R0402
R44, R49: 510; R0402
R45, R48, R52: 49.9k; R0402
R54, R55, R58, R60: 5.1k; R0402
R56: 5.6k; R0402
R67, R72, R76, R82, R83: 1.0M; R0402
R93: 1.2k; R0402
R97: 510; R0603
R99: 20kB; BOURNS_SLIDER
R105: 50kB; ALPS_POT_NARROW
R107: 10kB; ALPS_POT_NARROW

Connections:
1_TO_2: R58.2; also elsewhere on the board
2_TO_3: IC7.8 (OUT), R56.1; also elsewhere on the board
AREF_+10: R63.2, R105.P$1 (E); also elsewhere on the board
AREF_-2.5: R20.2, R45.2, R76.1; also elsewhere on the board
FOO1: IC5.7 (IN), R45.1, R49.2
GND: C3.2, C25.2, C27.2, IC7.3 (+IN), IC7.5 (+IN), IC7.10 (+IN), IC7.12 (+IN), IC10.12 (+IN), J2.P1 (1), J6.P1 (1), J6.P2 (2), J10.P1 (1), R3.1, R12.2, R83.1, R93.2, R99.3 (E), R105.P$3 (A); also elsewhere on the board
unnamed: J6.P3 (3), R48.2
unnamed: IC10.3 (+IN), R82.2, R83.2
unnamed: J2.P3 (3), R97.1
unnamed: C25.1, R44.1
unnamed: J10.P2 (2), R63.1
unnamed: IC5.10 (IN), R44.2, R48.1
unnamed: IC5.6 (CTRL), R107.P$2 (S)
unnamed: C40.1, IC7.6 (-IN), R54.1, R58.1, R60.2
unnamed: R3.2, R107.P$3 (A)
unnamed: R8.1, R99.2 (S)
unnamed: IC10.1 (OUT), LED2.K (C)
unnamed: IC10.2 (-IN), LED2.A, R93.1
unnamed: IC7.9 (-IN), R55.1, R56.2
unnamed: J2.P2 (2), R55.2
unnamed: C31.2, IC7.14 (OUT), R52.1, R54.2
unnamed: J10.P3 (3), R8.2
unnamed: C27.1, R49.1
unnamed: C33.1, IC5.5 (OUT), IC7.2 (-IN), R14.1, R20.1, R99.1 (A)
unnamed: C31.1, IC5.12 (OUT), IC7.13 (-IN), R52.2
unnamed: D5.A, R12.1, R72.2, R99.E (C)
unnamed: IC10.14 (OUT), R79.1
unnamed: IC10.13 (-IN), R67.2, R72.1, R76.2
unnamed: C33.2, IC5.11 (CTRL), IC7.1 (OUT), R67.1, R107.P$1 (E)
unnamed: C3.1, R14.2, R105.P$2 (S)
OUT2: C40.2, IC7.7 (OUT), R60.1, R82.1, R97.2
PROT2: D5.C, R79.2, R99.B (A)

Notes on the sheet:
Channel 2
Émilie Gillet
cc-by-sa
emilie.o.gillet@gmail.com

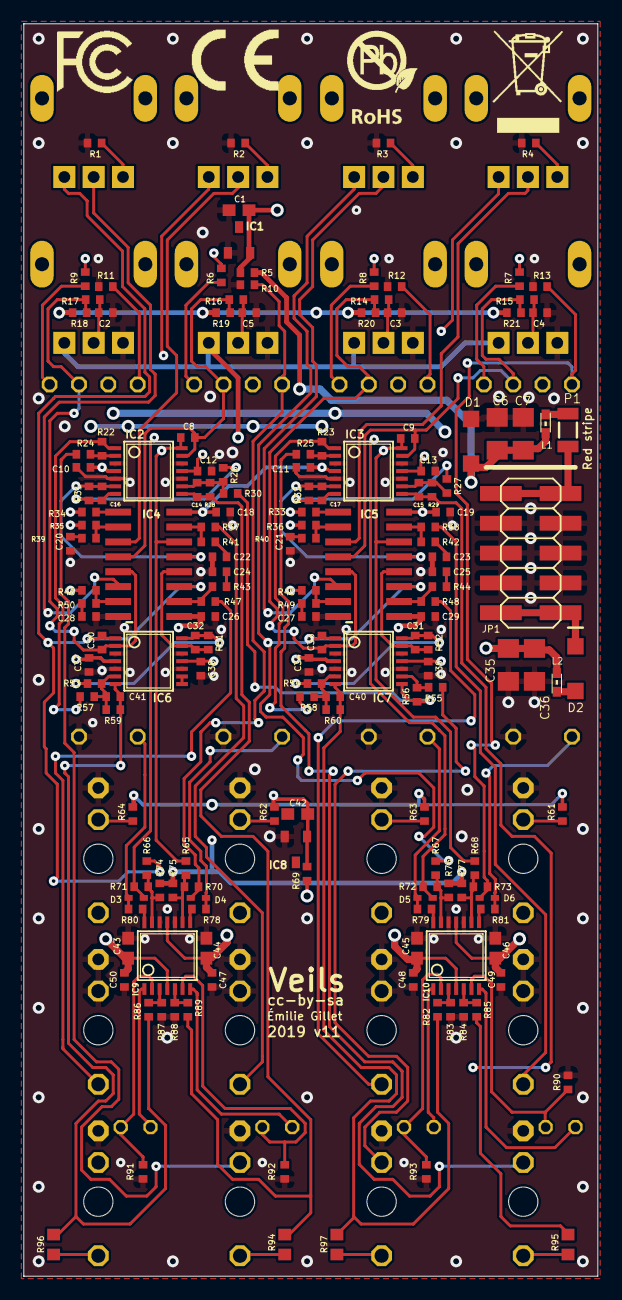
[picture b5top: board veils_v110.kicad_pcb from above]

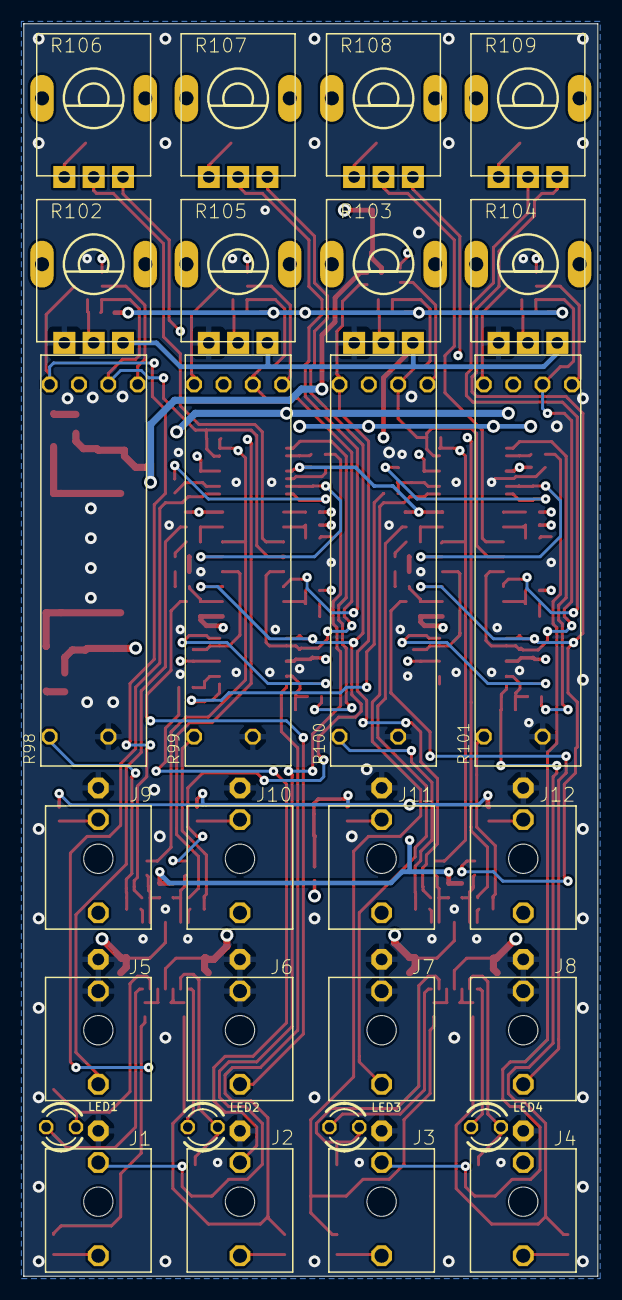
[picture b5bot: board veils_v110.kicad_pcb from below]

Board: 4 copper layers, 48.9 x 106.7 mm, 199 parts (28 on the bottom side), 121 nets.

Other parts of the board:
U$1: CE_MEDIUM
U$2: FCC_MEDIUM
U$3: ROHS_LOGO
U$4: TRASHCAN_LOGO

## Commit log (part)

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2025-08-08 Some converted to XML
2025-08-08 More converted
2025-08-13 Remove .gitmodules (no submodules exist)
2025-08-18 Some more converted to XML
2025-08-26 More conversions
2025-08-26 All converted
2025-08-26 Updating
2025-08-29 Added some panels
